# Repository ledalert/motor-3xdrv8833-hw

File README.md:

# motor-3xdrv8833-hw
Small stepper/dc motor driver board with 3 drv8833

This is still early prototype development. Will add more information once this prototype have been tested.

### Update 2015-07-30
#### Prototype boards have arrived
Silk width was a bit too thin and testing of the boards will be done in the near future.

### Update 2015-07-20
####Prototype boards have been ordered

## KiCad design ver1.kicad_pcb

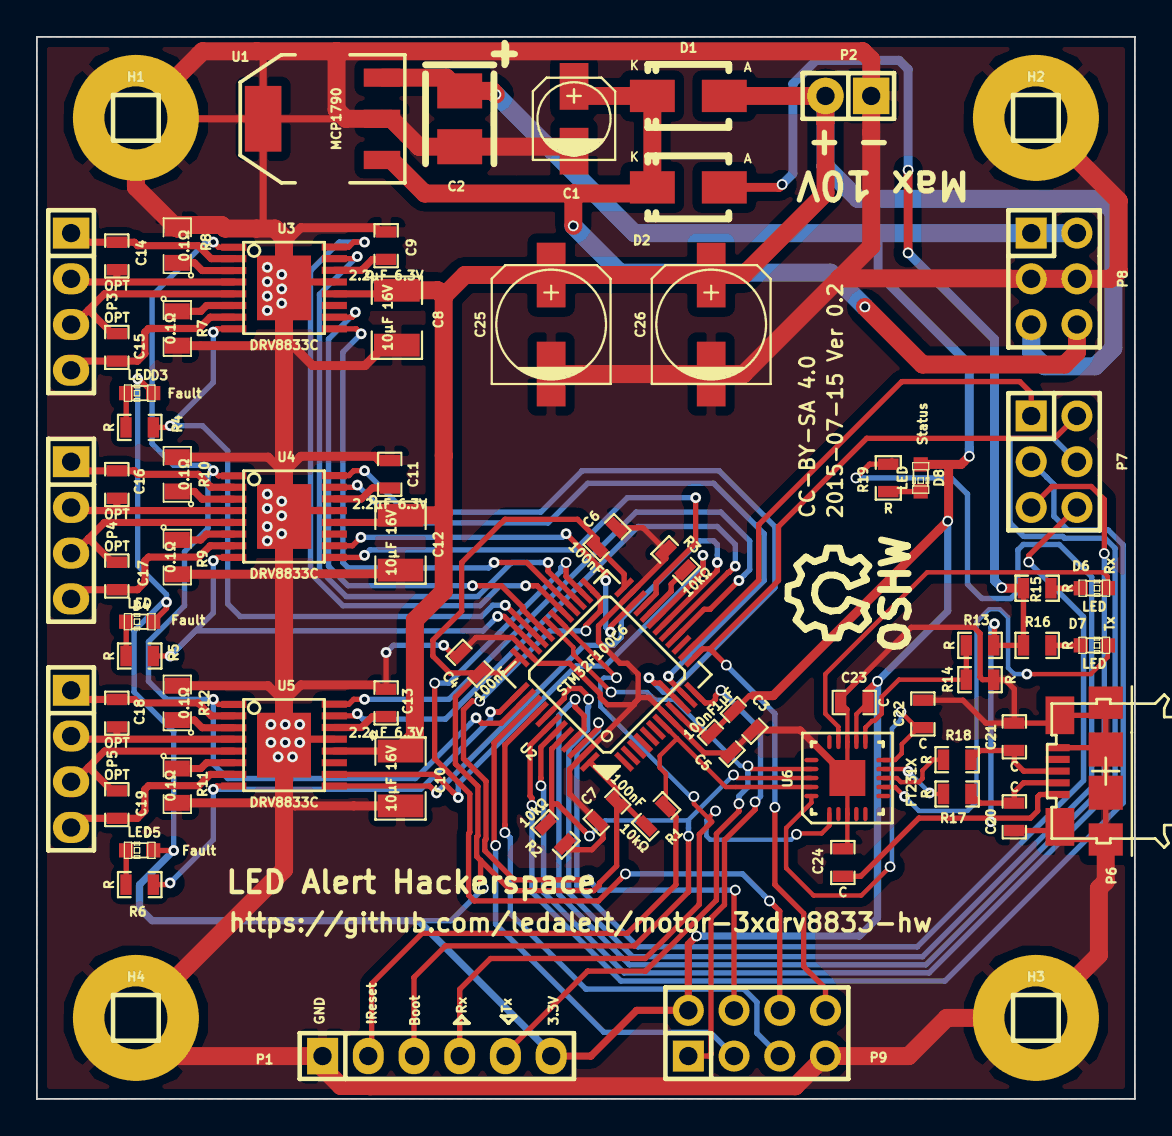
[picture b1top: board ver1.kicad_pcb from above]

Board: 2 copper layers, 61.0 x 59.0 mm, 73 parts (0 on the bottom side), 73 nets.

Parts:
C1: 1µF 35V; c_elec_4x5.3
C2: 1µF 6.3V; TantalC_SizeB_EIA-3528_Reflow
C3: 1µF; SMD-0603_c
C4, C5, C6, C7: 100nF; SMD-0603_c
C8, C10, C12: 10µF 16V; SMD-1210
C9, C11, C13: 2.2µF 6.3V; SMD-0603_c
C14, C15, C16, C17, C18, C19: OPT; SMD-0603_c
C20, C21, C22, C23, C24: C; SMD-0603_c
C25, C26: 220µF 16V; c_elec_6.3x7.7
D1, D2: DIODESCH; Diode-SMA_Standard
D3, D4, D5, D6, D7, D8: LED; LED-0603
H1, H2, H3, H4: CONN_1; Pin_Header_Straight_1x01
P1: CONN_6; Pin_Header_Straight_1x06
P2: CONN_2; Pin_Header_Straight_1x02
P3, P4, P5: CONN_4; Pin_Header_Straight_1x04
P6: USB_Micro_B; USB MICRO B
P7, P8: CONN_3X2; Pin_Header_Straight_2x03
P9: CONN_4X2; Pin_Header_Straight_2x04
R1, R2, R3: 10kΩ; SMD-0603_r
R4, R5, R6, R13, R14, R15, R16, R17, R18, R19: R; SMD-0603_r
R7, R8, R9, R10, R11, R12: 0.1Ω; SMD-0805
SYM: Symbol_OSHW-Logo_SilkScreen_07Jul2012; Symbol_OSHW-Logo_SilkScreen
U1: MCP1790; SOT-223
U2: STM32F100C6; lqfp-48
U3, U4, U5: DRV8833C; SSOP-16(EP)
U6: FT231X; QFN_20-1EP

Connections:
/BOOT1: R3.1, U2.20
/ESP8266 PTH Connector/CH_PD: P9.6, U2.26
/ESP8266 PTH Connector/GPIO0: P9.3, U2.39
/ESP8266 PTH Connector/GPIO2: P9.5, U2.40
/ESP8266 PTH Connector/RST: P9.4, U2.25
/ESP8266 PTH Connector/RXD: P9.1, U2.12
/ESP8266 PTH Connector/TXD: P7.2, P9.8, U2.13
/GPIO1: P7.1, U2.14
/GPIO5: P7.3, U2.42
/GPIO6: P7.4, U2.43
/GPIO7: P7.5, U2.45
/GPIO8: P7.6, U2.46
/PC Interface/DTR: P1.3, R2.1, U2.44, U6.18
/PC Interface/RTS: P1.2, R1.2, U2.7, U6.19
/PC Interface/RX: P1.4, U2.30, U6.1
/PC Interface/TX: P1.5, U2.31, U6.17
/PC Interface/VBUS: C24.1, D2.1, P6.1, R13.2, R15.2, R16.2
/STATUS_LED: R19.2, U2.41
/VDD_INT: C1.1, D1.2, D2.2, P8.6, U1.1
/drv8833_1/AIN1: U2.29, U3.16
/drv8833_1/AIN2: U2.27, U3.15
/drv8833_1/AOUT1: C14.2, P3.1, U3.2
/drv8833_1/AOUT2: C14.1, P3.2, U3.4
/drv8833_1/BIN1: U2.28, U3.9
/drv8833_1/BIN2: U2.32, U3.10
/drv8833_1/BOUT1: C15.2, P3.4, U3.7
/drv8833_1/BOUT2: C15.1, P3.3, U3.5
/drv8833_1/FAULT_OUT: R4.2, U2.33, U3.8
/drv8833_1/SLEEP_IN: U2.38, U3.1, U4.1, U5.1
/drv8833_2/AIN1: U2.10, U4.16
/drv8833_2/AIN2: U2.11, U4.15
/drv8833_2/AOUT1: C16.2, P4.1, U4.2
/drv8833_2/AOUT2: C16.1, P4.2, U4.4
/drv8833_2/BIN1: U2.21, U4.9
/drv8833_2/BIN2: U2.22, U4.10
/drv8833_2/BOUT1: C17.2, P4.4, U4.7
/drv8833_2/BOUT2: C17.1, P4.3, U4.5
/drv8833_2/FAULT_OUT: R5.2, U2.34, U4.8
/drv8833_3/AIN1: U2.16, U5.16
/drv8833_3/AIN2: U2.17, U5.15
/drv8833_3/AOUT1: C18.2, P5.1, U5.2
/drv8833_3/AOUT2: C18.1, P5.2, U5.4
/drv8833_3/BIN1: U2.18, U5.9
/drv8833_3/BIN2: U2.19, U5.10
/drv8833_3/BOUT1: C19.2, P5.4, U5.7
/drv8833_3/BOUT2: C19.1, P5.3, U5.5
/drv8833_3/FAULT_OUT: R6.2, U2.37, U5.8
GND: C1.2, C2.2, C3.2, C4.2, C5.2, C6.2, C7.2, C8.2, C9.2, C10.2, C11.2, C12.2, C13.2, C20.2, C21.2, C22.2, C23.2, C24.2, C25.2, C26.2, H1.1, H2.1, H3.1, H4.1, P1.1, P2.1, P6.5, P6.S, P8.3, P8.4, P9.7, R2.2, R3.2, R7.2, R8.2, R9.2, R10.2, R11.2, R12.2, R14.1, U1.2, U1.4, U2.8, U2.23, U2.35, U2.47, U3.13, U3.17, U4.13, U4.17, U5.13, U5.17, U6.3, U6.13, U6.21
unnamed: C9.1, U3.14
unnamed: C11.1, U4.14
unnamed: C13.1, U5.14
unnamed: C20.1, P6.2, R17.2
unnamed: C21.1, P6.3, R18.2
unnamed: C22.1, U6.10, U6.20
unnamed: D3.2, R4.1
unnamed: D4.2, R5.1
unnamed: D5.2, R6.1
unnamed: D6.1, R15.1
unnamed: D6.2, U6.14
unnamed: D7.1, R16.1
unnamed: D7.2, U6.7
unnamed: D8.2, R19.1
unnamed: R7.1, U3.6
unnamed: R8.1, U3.3
unnamed: R9.1, U4.6
unnamed: R10.1, U4.3
unnamed: R11.1, U5.6
unnamed: R12.1, U5.3
unnamed: R13.1, R14.2, U6.11
unnamed: R17.1, U6.9
unnamed: R18.1, U6.8
VCC: C2.1, C3.1, C4.1, C5.1, C6.1, C7.1, C23.1, D3.1, D4.1, D5.1, D8.1, P1.6, P8.1, P8.2, P9.2, R1.1, U1.3, U2.9, U2.24, U2.36, U2.48, U6.12
VDD: C8.1, C10.1, C12.1, C25.1, C26.1, D1.1, P2.2, P8.5, U3.12, U4.12, U5.12

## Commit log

2015-07-11 Done some routing, added fault indicators
2015-07-11 Converted doc to spaces instead of tabs
2015-07-11 Added footprints, checking in before redoing routing
2015-07-11 Tried a new layout for motor driver output
2015-07-11 Rerouted motor output
2015-07-19 Added PC interface and did some routing
2015-07-19 Final routing complete
2015-07-19 Updated schematics PDF
2015-07-20 Final changes for v0.21

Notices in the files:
ver1.kicad_pcb:
CC-BY-SA 4.0
